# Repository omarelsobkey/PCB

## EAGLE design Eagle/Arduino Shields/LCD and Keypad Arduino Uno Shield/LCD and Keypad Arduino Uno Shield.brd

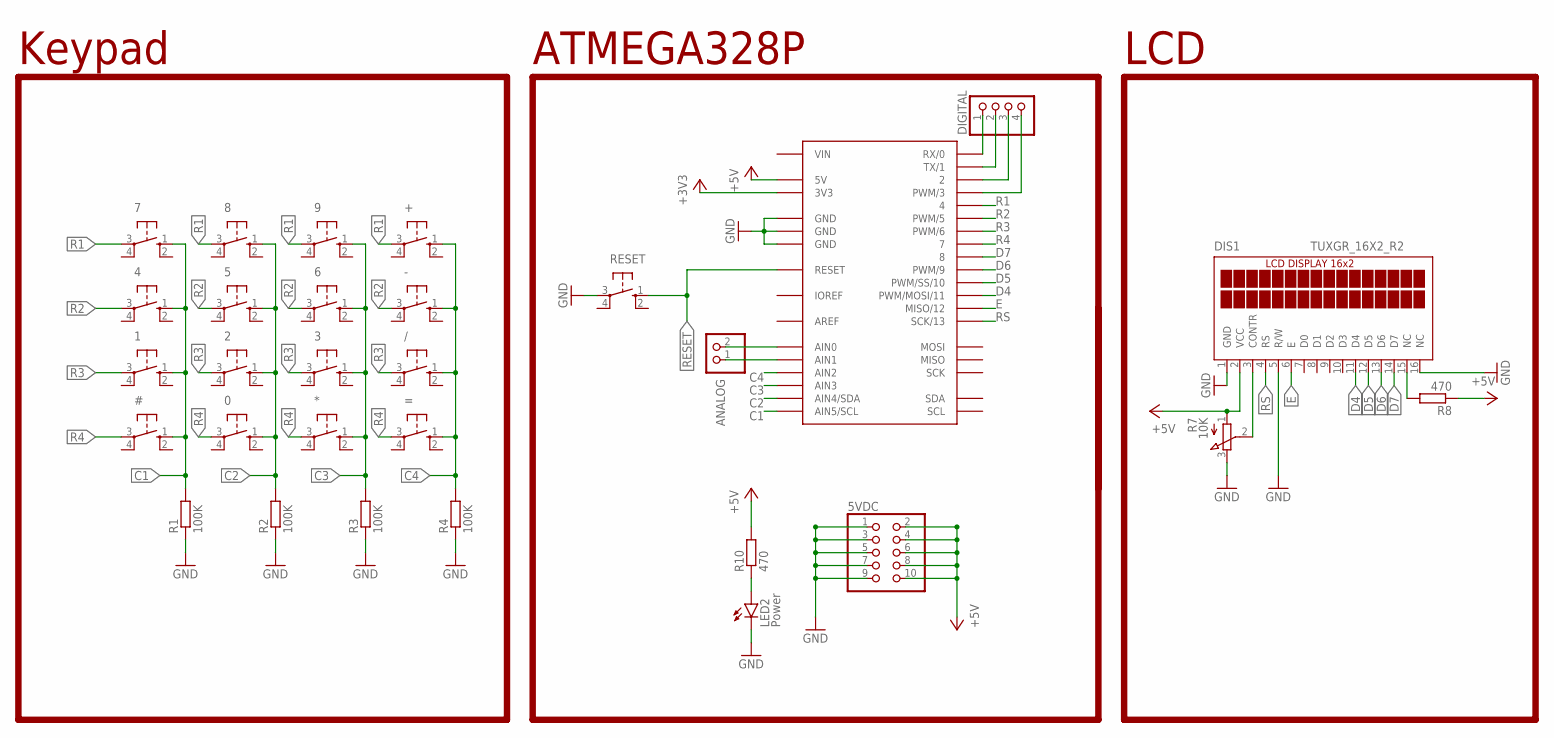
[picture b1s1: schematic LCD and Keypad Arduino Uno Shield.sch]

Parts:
0, 1, 2, 3, 4, 5, 6, 7, 8, 9: 10-XX; B3F-10XX
5VDC: PINHD-2X5; 2X05
#: 10-XX; B3F-10XX
*: 10-XX; B3F-10XX
+: 10-XX; B3F-10XX
-: 10-XX; B3F-10XX
/: 10-XX; B3F-10XX
=: 10-XX; B3F-10XX
ANALOG: PINHD-1X2; 1X02
ARD1: A-UNO_ISP-TP; A-UNO-ISP_TP
DIGITAL: PINHD-1X4; 1X04
DIS1: TUXGR_16X2_R2
LED2: Power; LED3MM
R1, R2, R3, R4: 100K; 0204/7
R7: 10K; 3RP/1610N
R8, R10: 470; 0204/7
RESET: 10-XX; B3F-10XX

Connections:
+3V3: ARD1.3V3
+5V: 5VDC.2, 5VDC.4, 5VDC.6, 5VDC.8, 5VDC.10, ARD1.5V, DIS1.2 (VCC), R7.1 (A), R8.1, R10.2
AREF: ARD1.AREF
C1: 1.1 (S), 4.1 (S), 7.1 (S), #.1 (S), ARD1.A5 (AIN5/SCL), R1.2
C2: 0.1 (S), 2.1 (S), 5.1 (S), 8.1 (S), ARD1.A4 (AIN4/SDA), R2.2
C3: 3.1 (S), 6.1 (S), 9.1 (S), *.1 (S), ARD1.A3 (AIN3), R3.2
C4: +.1 (S), -.1 (S), /.1 (S), =.1 (S), ARD1.A2 (AIN2), R4.2
D4: ARD1.11 (PWM/MOSI/11), DIS1.11 (D4)
D5: ARD1.10 (PWM/SS/10), DIS1.12 (D5)
D6: ARD1.9 (PWM/9), DIS1.13 (D6)
D7: ARD1.8, DIS1.14 (D7)
E: ARD1.12 (MISO/12), DIS1.6 (E)
GND: 5VDC.1, 5VDC.3, 5VDC.5, 5VDC.7, 5VDC.9, ARD1.GND@1 (GND), ARD1.GND@2 (GND), ARD1.GND@3 (GND), DIS1.1 (GND), DIS1.5 (R/W), DIS1.16 (NC), LED2.K (C), R1.1, R2.1, R3.1, R4.1, R7.3 (E), RESET.3
IOREF: ARD1.IOREF
unnamed: ANALOG.1, ARD1.A1 (AIN1)
unnamed: ANALOG.2, ARD1.A0 (AIN0)
unnamed: DIS1.3 (CONTR), R7.2 (S)
unnamed: DIS1.15 (NC), R8.2
unnamed: ARD1.3 (PWM/3), DIGITAL.4
unnamed: ARD1.2, DIGITAL.3
unnamed: ARD1.1 (TX/1), DIGITAL.2
unnamed: LED2.A, R10.1
unnamed: ARD1.0 (RX/0), DIGITAL.1
R1: 7.3, 8.3, 9.3, +.3, ARD1.4
R2: 4.3, 5.3, 6.3, -.3, ARD1.5 (PWM/5)
R3: 1.3, 2.3, 3.3, /.3, ARD1.6 (PWM/6)
R4: 0.3, #.3, *.3, =.3, ARD1.7
RESET: ARD1.RST (RESET), RESET.1 (S)
RS: ARD1.13 (SCK/13), DIS1.4 (RS)
VIN: ARD1.VIN

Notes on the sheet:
Keypad
LCD
ATMEGA328P

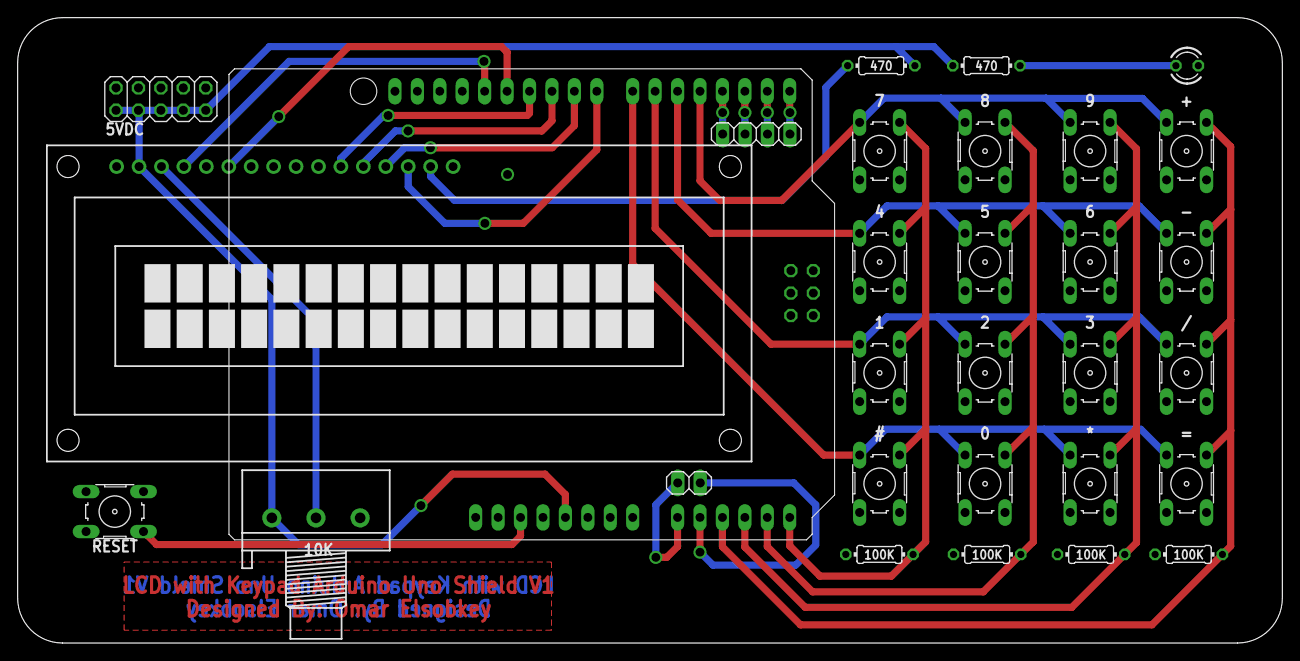
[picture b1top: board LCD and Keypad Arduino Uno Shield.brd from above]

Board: 2 copper layers, 143.2 x 70.8 mm, 30 parts (0 on the bottom side), 26 nets.

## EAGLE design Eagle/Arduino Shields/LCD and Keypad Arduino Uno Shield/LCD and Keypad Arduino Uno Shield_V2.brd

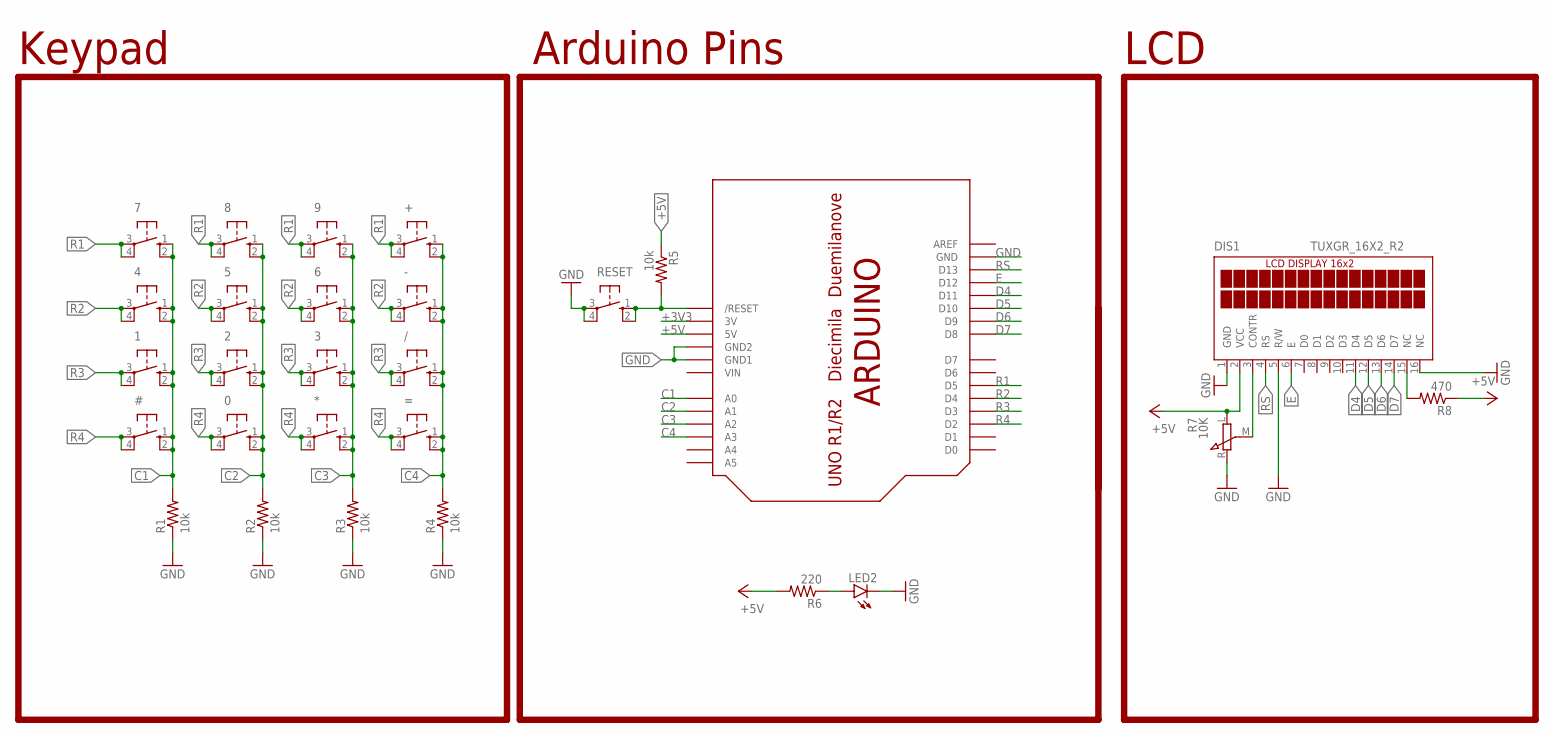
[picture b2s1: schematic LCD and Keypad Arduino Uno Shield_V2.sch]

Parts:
0, 1, 2, 3, 4, 5, 6, 7, 8, 9: 10-XX; B3F-10XX
#: 10-XX; B3F-10XX
*: 10-XX; B3F-10XX
+: 10-XX; B3F-10XX
-: 10-XX; B3F-10XX
/: 10-XX; B3F-10XX
=: 10-XX; B3F-10XX
DIS1: TUXGR_16X2_R2
LED2: LEDSML0805; SML0805
R1, R2, R3, R4, R5: 10k; 1206
R6: 220; 1206
R7: 10K; RM-065
R8: 470; 1206
RESET: 10-XX; B3F-10XX
U$1: ARDUINO-NODIM

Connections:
+3V3: U$1.3V
+5V: DIS1.2 (VCC), R5.1, R6.2, R7.L, R8.1, U$1.5V
C1: 1.1 (S), 1.2 (S1), 4.1 (S), 4.2 (S1), 7.1 (S), 7.2 (S1), #.1 (S), #.2 (S1), R1.2, U$1.A0
C2: 0.1 (S), 0.2 (S1), 2.1 (S), 2.2 (S1), 5.1 (S), 5.2 (S1), 8.1 (S), 8.2 (S1), R2.2, U$1.A1
C3: 3.1 (S), 3.2 (S1), 6.1 (S), 6.2 (S1), 9.1 (S), 9.2 (S1), *.1 (S), *.2 (S1), R3.2, U$1.A2
C4: +.1 (S), +.2 (S1), -.1 (S), -.2 (S1), /.1 (S), /.2 (S1), =.1 (S), =.2 (S1), R4.2, U$1.A3
D4: DIS1.11 (D4), U$1.D11
D5: DIS1.12 (D5), U$1.D10
D6: DIS1.13 (D6), U$1.D9
D7: DIS1.14 (D7), U$1.D8
E: DIS1.6 (E), U$1.D12
GND: DIS1.1 (GND), DIS1.5 (R/W), DIS1.16 (NC), LED2.C, R1.1, R2.1, R3.1, R4.1, R7.R, RESET.3, RESET.4 (P1), U$1.GND, U$1.GND1, U$1.GND2
unnamed: DIS1.3 (CONTR), R7.M
unnamed: DIS1.15 (NC), R8.2
unnamed: LED2.A, R6.1
R1: 7.3, 7.4 (P1), 8.3, 8.4 (P1), 9.3, 9.4 (P1), +.3, +.4 (P1), U$1.D5
R2: 4.3, 4.4 (P1), 5.3, 5.4 (P1), 6.3, 6.4 (P1), -.3, -.4 (P1), U$1.D4
R3: 1.3, 1.4 (P1), 2.3, 2.4 (P1), 3.3, 3.4 (P1), /.3, /.4 (P1), U$1.D3
R4: 0.3, 0.4 (P1), #.3, #.4 (P1), *.3, *.4 (P1), =.3, =.4 (P1), U$1.D2
RESET: R5.2, RESET.1 (S), RESET.2 (S1), U$1.RESET (/RESET)
RS: DIS1.4 (RS), U$1.D13
VIN: U$1.VIN

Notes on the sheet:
Keypad
LCD
Arduino Pins

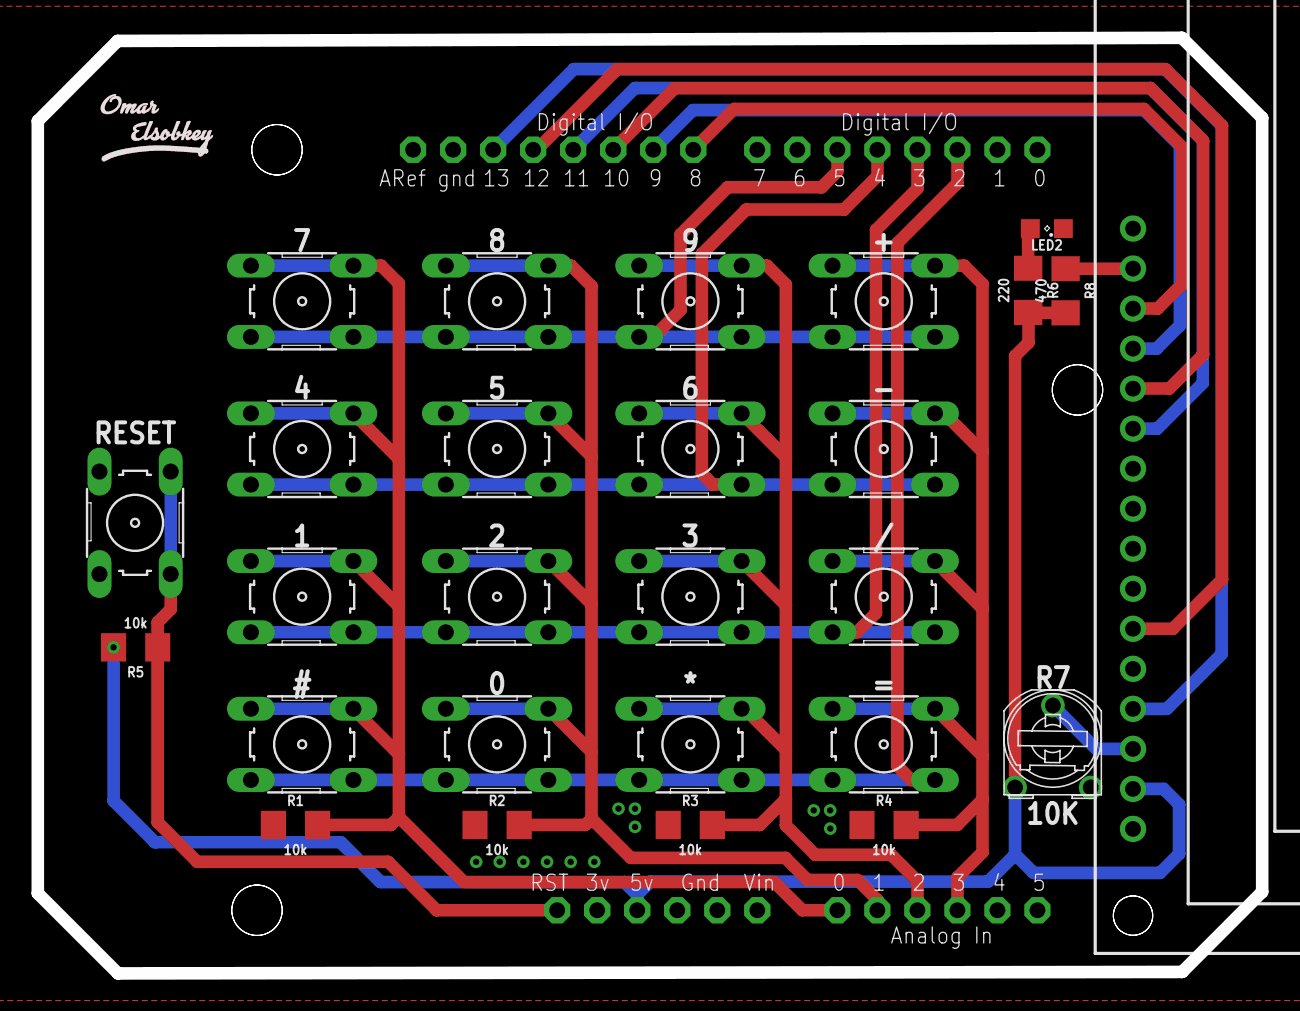
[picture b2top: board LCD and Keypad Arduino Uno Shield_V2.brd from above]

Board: 2 copper layers, 77.7 x 59.4 mm, 29 parts (0 on the bottom side), 20 nets.

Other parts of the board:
U$2: OMAR_ELSOBKEY_X0.5

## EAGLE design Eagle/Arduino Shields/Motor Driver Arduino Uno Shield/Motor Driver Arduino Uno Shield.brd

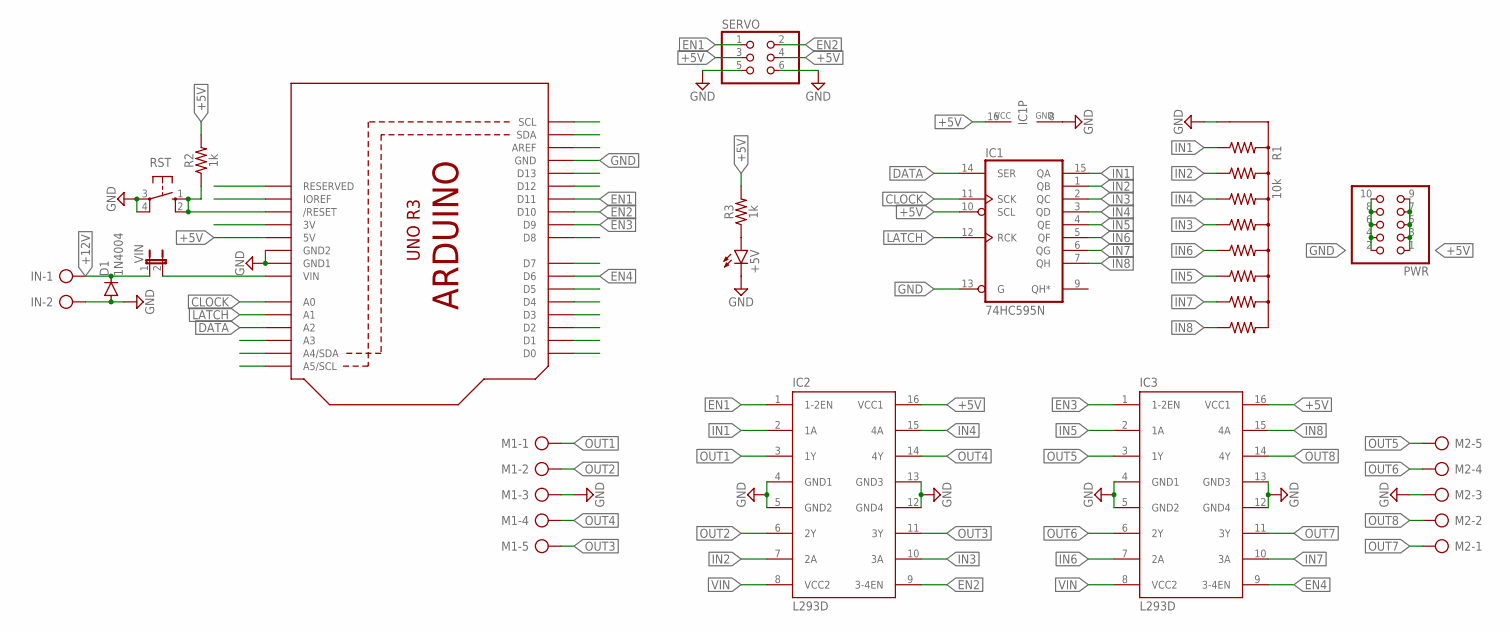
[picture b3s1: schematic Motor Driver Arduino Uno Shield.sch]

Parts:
+5V: LEDCHIP-LED0805; CHIP-LED0805
D1: 1N4004; DO41-10
IC1: 74HC595N; DIL16
IC2, IC3: L293D; DIL16
IN: AK500/2-H
M1, M2: AK500/5-H
PWR: PINHD-2X5; 2X05
R1: 10k; 4609X-101-103LF
R2, R3: 1k; 1206
RST: 10-XX; B3F-10XX
SERVO: PINHD-2X3; 2X03
U1: ARDUINOR3-BPLACE
VIN: JP1E; JP1

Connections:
+5V: IC1.10 (SCL), IC1.16 (VCC), IC2.16 (VCC1), IC3.16 (VCC1), PWR.1, PWR.3, PWR.5, PWR.7, PWR.9, R2.2, R3.2, SERVO.3, SERVO.4, U1.5V
+12V: D1.C, IN.1, VIN.1
AREF: U1.AREF
CLOCK: IC1.11 (SCK), U1.A0
D2: U1.D2
D3: U1.D3
D4: U1.D4
D5: U1.D5
D7: U1.D7
D8: U1.D8
D12: U1.D12
D13: U1.D13
DATA: IC1.14 (SER), U1.A2
EN1: IC2.1 (1-2EN), SERVO.1, U1.D11
EN2: IC2.9 (3-4EN), SERVO.2, U1.D10
EN3: IC3.1 (1-2EN), U1.D9
EN4: IC3.9 (3-4EN), U1.D6
GND: +5V.C, D1.A, IC1.8 (GND), IC1.13 (G), IC2.4 (GND1), IC2.5 (GND2), IC2.12 (GND4), IC2.13 (GND3), IC3.4 (GND1), IC3.5 (GND2), IC3.12 (GND4), IC3.13 (GND3), IN.2, M1.3, M2.3, PWR.2, PWR.4, PWR.6, PWR.8, PWR.10, R1.1, RST.3, RST.4 (P1), SERVO.5, SERVO.6, U1.GND, U1.GND1, U1.GND2
IN1: IC1.15 (QA), IC2.2 (1A), R1.2
IN2: IC1.1 (QB), IC2.7 (2A), R1.3
IN3: IC1.2 (QC), IC2.10 (3A), R1.5
IN4: IC1.3 (QD), IC2.15 (4A), R1.4
IN5: IC1.4 (QE), IC3.2 (1A), R1.7
IN6: IC1.5 (QF), IC3.7 (2A), R1.6
IN7: IC1.6 (QG), IC3.10 (3A), R1.8
IN8: IC1.7 (QH), IC3.15 (4A), R1.9
LATCH: IC1.12 (RCK), U1.A1
unnamed: +5V.A, R3.1
OUT1: IC2.3 (1Y), M1.1
OUT2: IC2.6 (2Y), M1.2
OUT3: IC2.11 (3Y), M1.5
OUT4: IC2.14 (4Y), M1.4
OUT5: IC3.3 (1Y), M2.5
OUT6: IC3.6 (2Y), M2.4
OUT7: IC3.11 (3Y), M2.1
OUT8: IC3.14 (4Y), M2.2
RST: R2.1, RST.1 (S), RST.2 (S1), U1.RESET (/RESET)
SCL: U1.SCL
SDA: U1.SDA
VIN: IC2.8 (VCC2), IC3.8 (VCC2), U1.VIN, VIN.2

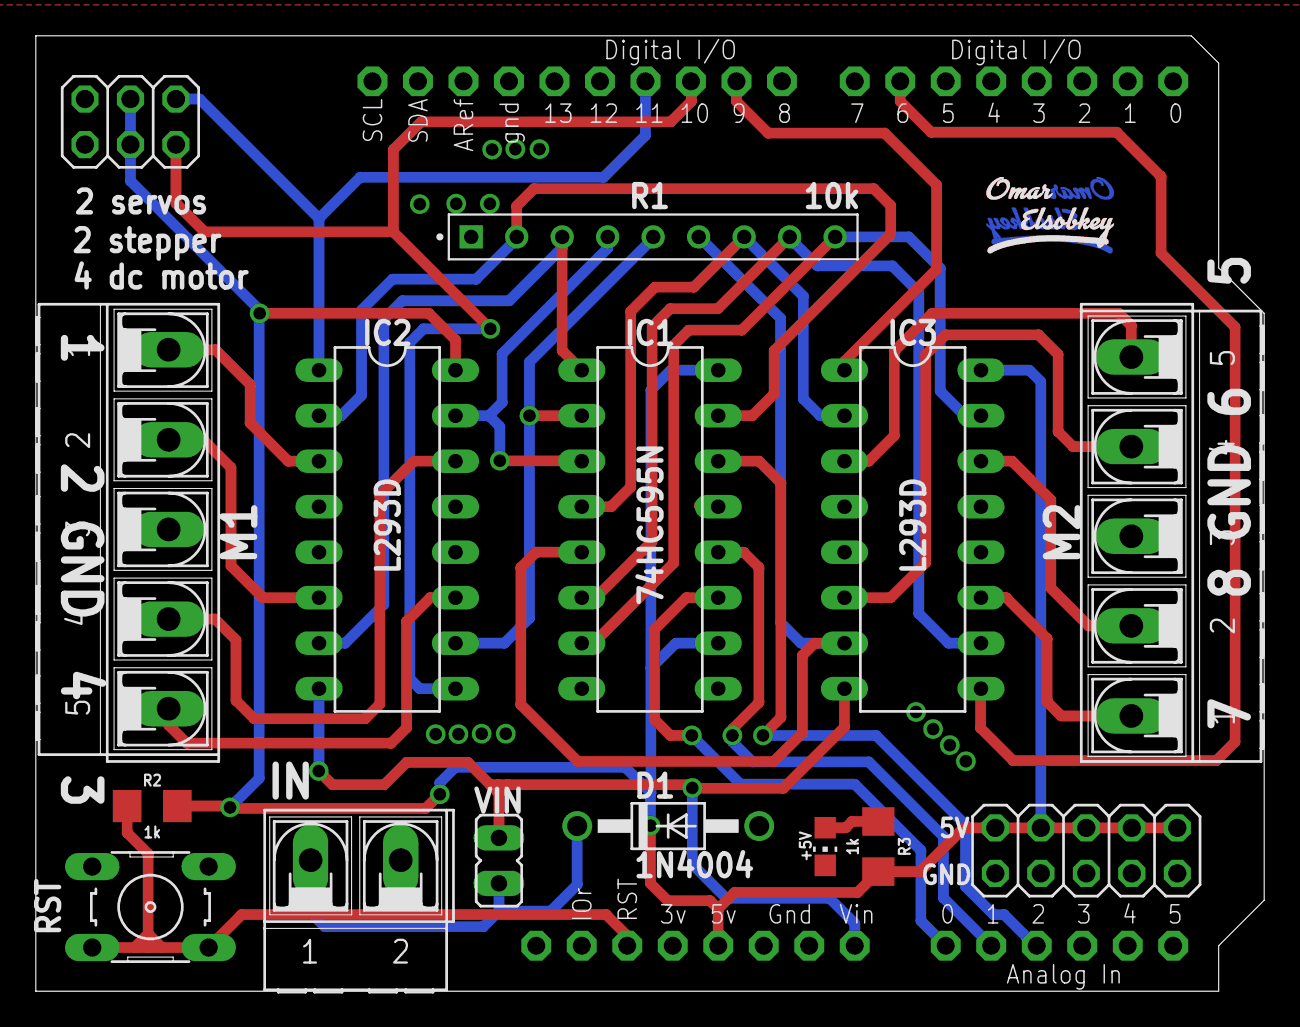
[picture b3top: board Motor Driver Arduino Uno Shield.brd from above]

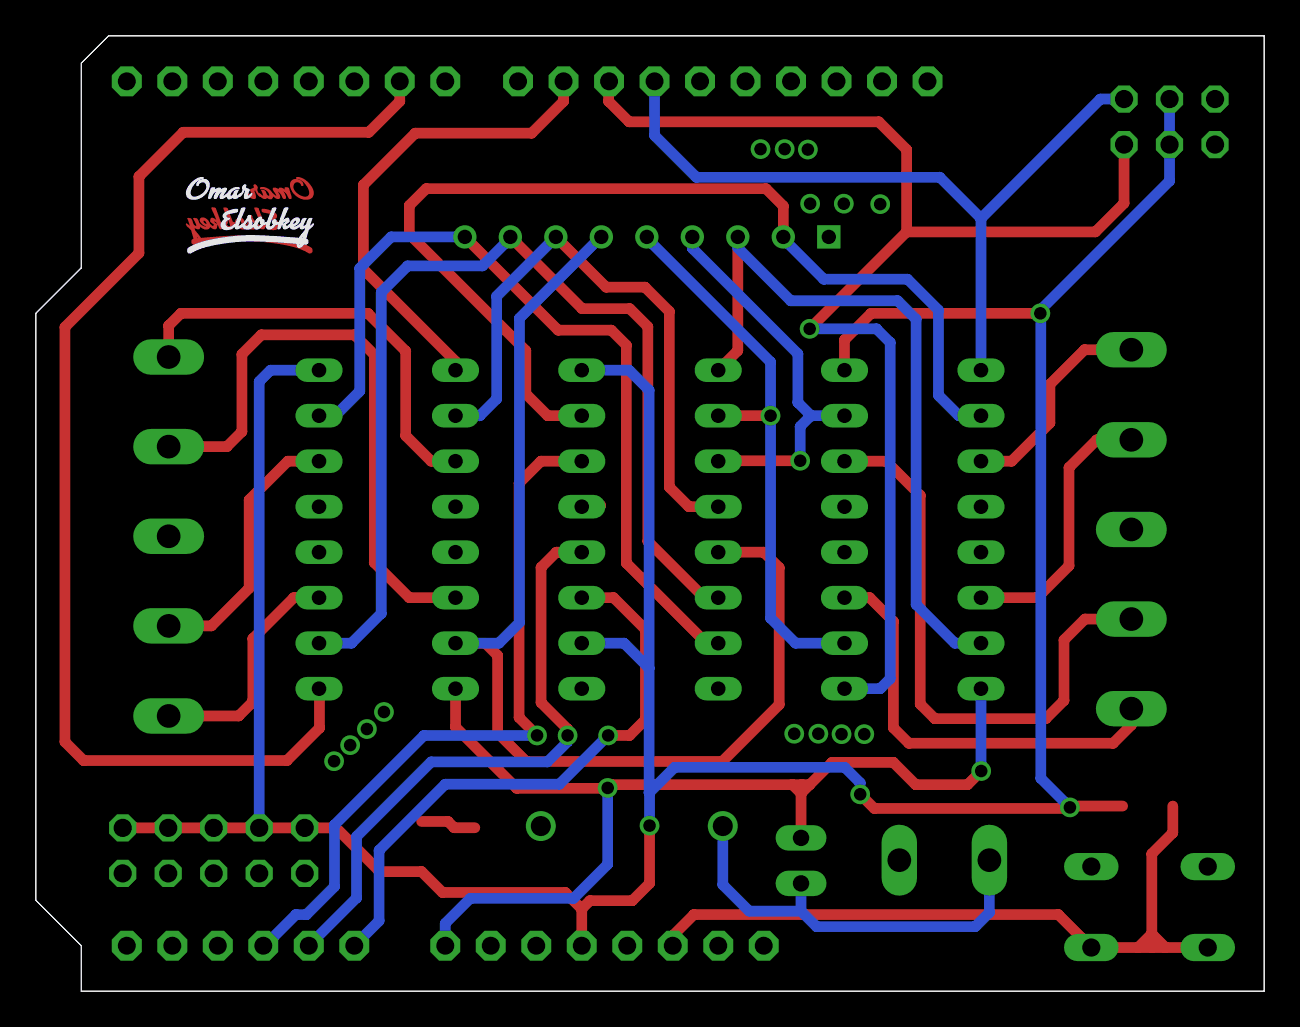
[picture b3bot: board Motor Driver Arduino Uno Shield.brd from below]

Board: 2 copper layers, 68.6 x 53.3 mm, 20 parts (2 on the bottom side), 29 nets.

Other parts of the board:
U$1, U$3: OMAR_ELSOBKEY_X0.5_TN
U$2, U$4: OMAR_ELSOBKEY_X0.5_T

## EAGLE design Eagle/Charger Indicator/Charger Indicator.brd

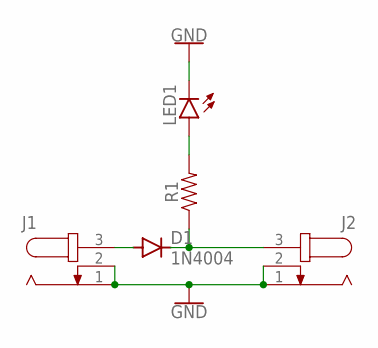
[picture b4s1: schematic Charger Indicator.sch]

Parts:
D1: 1N4004; DO41-10
J1, J2: JACK-PLUG0; SPC4077
LED1: LED3MM
R1: 1206

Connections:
GND: J1.1, J1.2, J2.1, J2.2, LED1.K (C)
unnamed: D1.A, J1.3
unnamed: D1.C, J2.3, R1.1
unnamed: LED1.A, R1.2

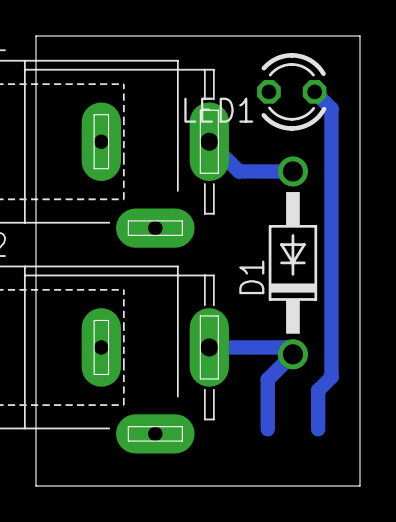
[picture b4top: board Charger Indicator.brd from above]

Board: 2 copper layers, 18.0 x 25.0 mm, 5 parts (1 on the bottom side), 4 nets.

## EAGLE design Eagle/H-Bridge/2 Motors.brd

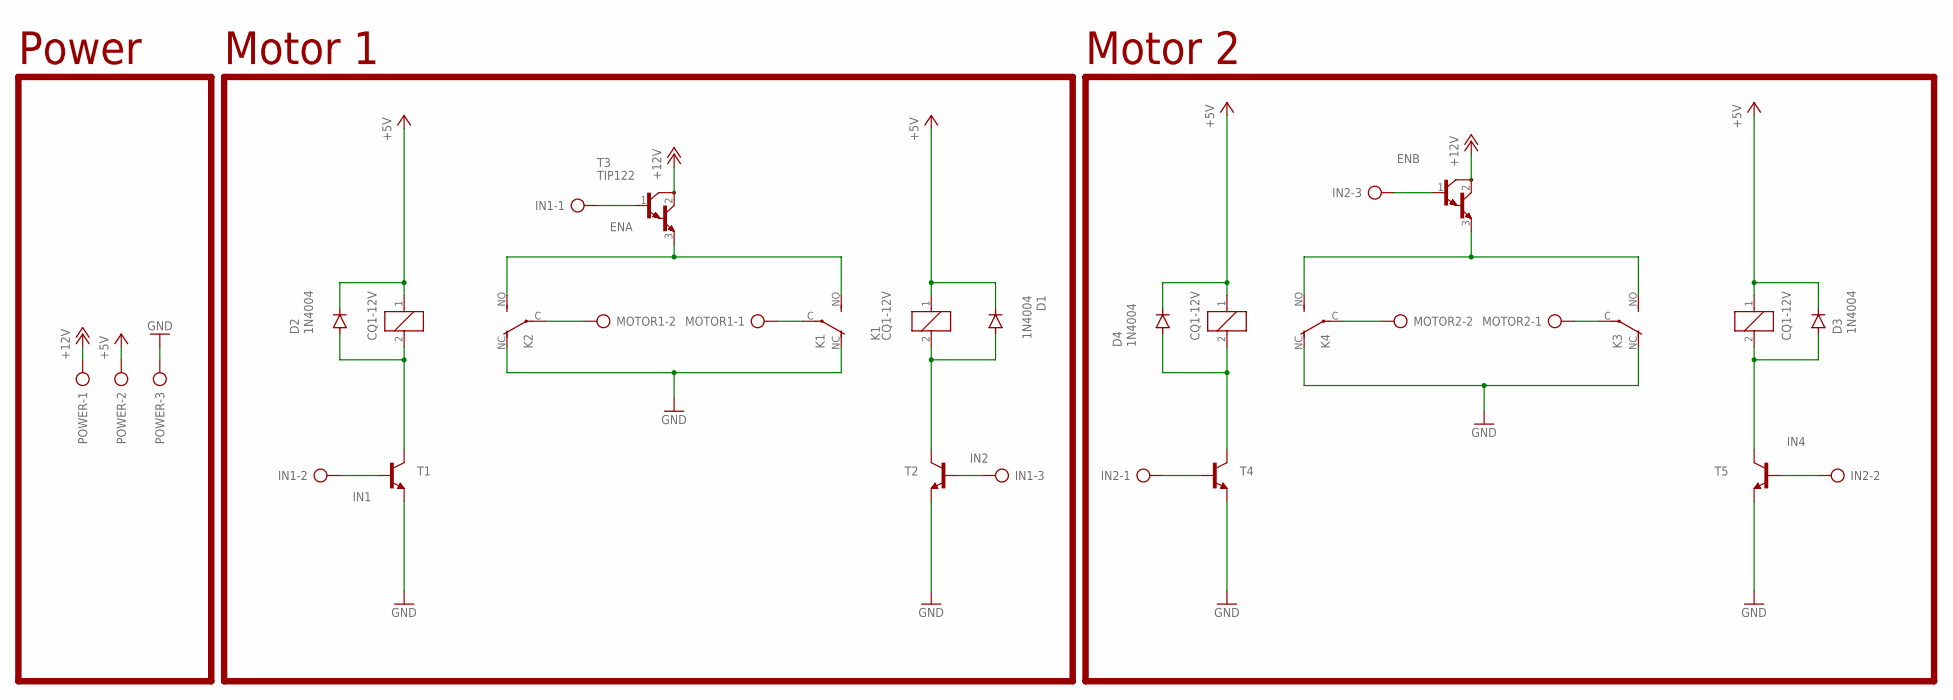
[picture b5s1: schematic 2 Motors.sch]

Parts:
D1, D2, D3, D4: 1N4004; DO41-10
IN1, IN2: AK300/3
K1, K2, K3, K4: CQ1-12V; CQ1
MOTOR1, MOTOR2: AK300/2
POWER: AK300/3
T1, T2, T4, T5: 2N2222-NPN-TO92-EBC; TO92-EBC
T3, T6: TIP122; TO220

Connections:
+5V: D1.C, D2.C, D3.C, D4.C, K1.1, K2.1, K3.1, K4.1, POWER.2
+12V: POWER.1, T3.2 (C), T6.2 (C)
ENA: IN1.1, T3.1 (B)
ENB: IN2.3, T6.1 (B)
GND: K1.NC (O), K2.NC (O), K3.NC (O), K4.NC (O), POWER.3, T1.E, T2.E, T4.E, T5.E
IN1: IN1.2, T1.B
IN2: IN1.3, T2.B
IN3: IN2.1, T4.B
IN4: IN2.2, T5.B
unnamed: K2.C, MOTOR1.2
unnamed: K1.NO (S), K2.NO (S), T3.3 (E)
unnamed: D2.A, K2.2, T1.C
unnamed: K1.C, MOTOR1.1
unnamed: D1.A, K1.2, T2.C
unnamed: D3.A, K3.2, T5.C
unnamed: K3.NO (S), K4.NO (S), T6.3 (E)
unnamed: D4.A, K4.2, T4.C
unnamed: K3.C, MOTOR2.1
unnamed: K4.C, MOTOR2.2

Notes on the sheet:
Power
Motor 1
Motor 2

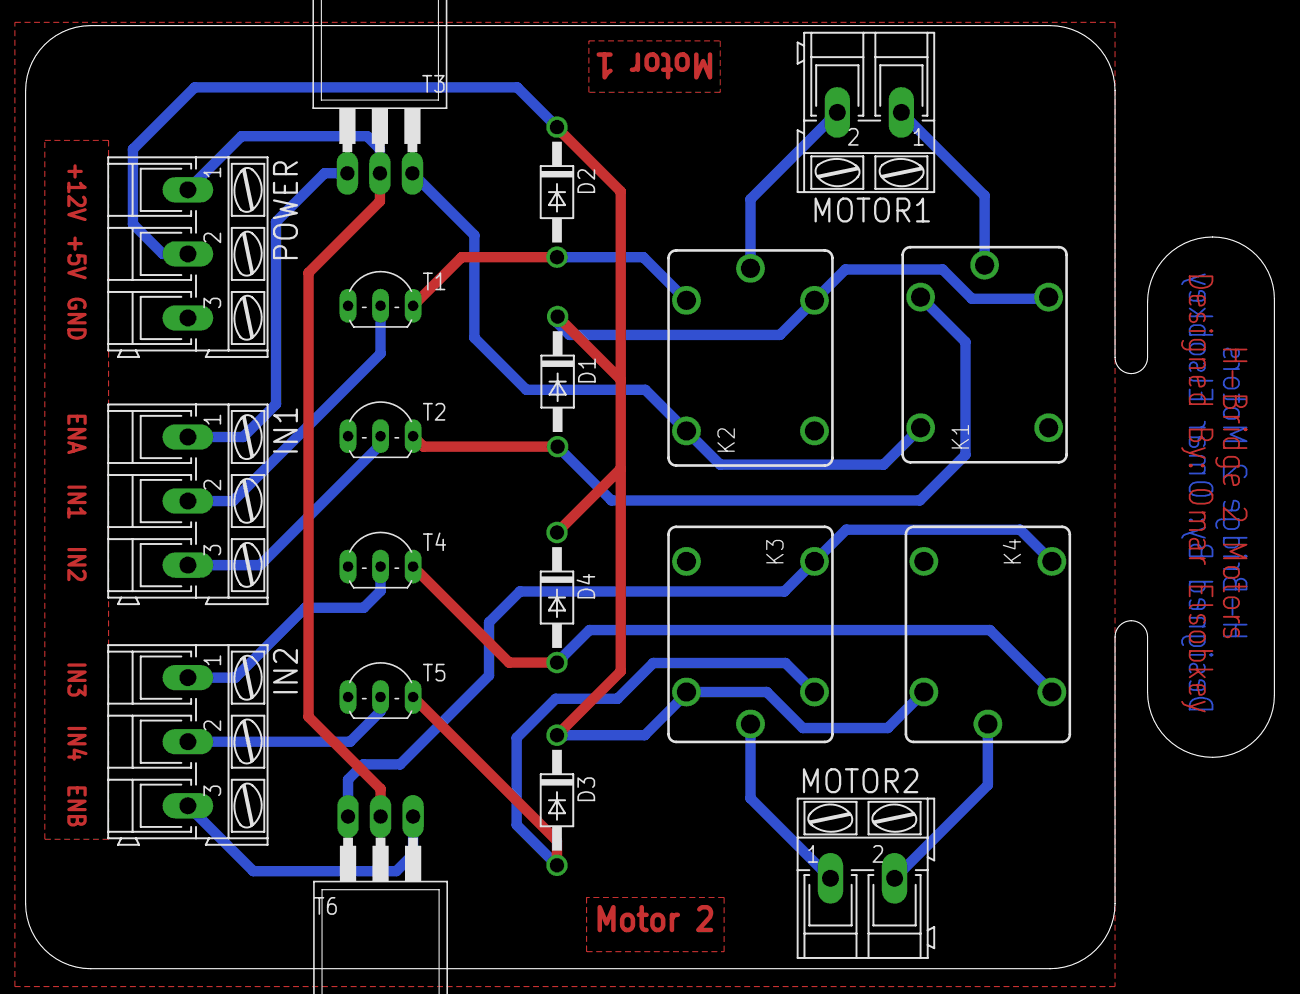
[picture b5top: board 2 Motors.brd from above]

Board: 2 copper layers, 97.5 x 73.7 mm, 19 parts (0 on the bottom side), 19 nets.

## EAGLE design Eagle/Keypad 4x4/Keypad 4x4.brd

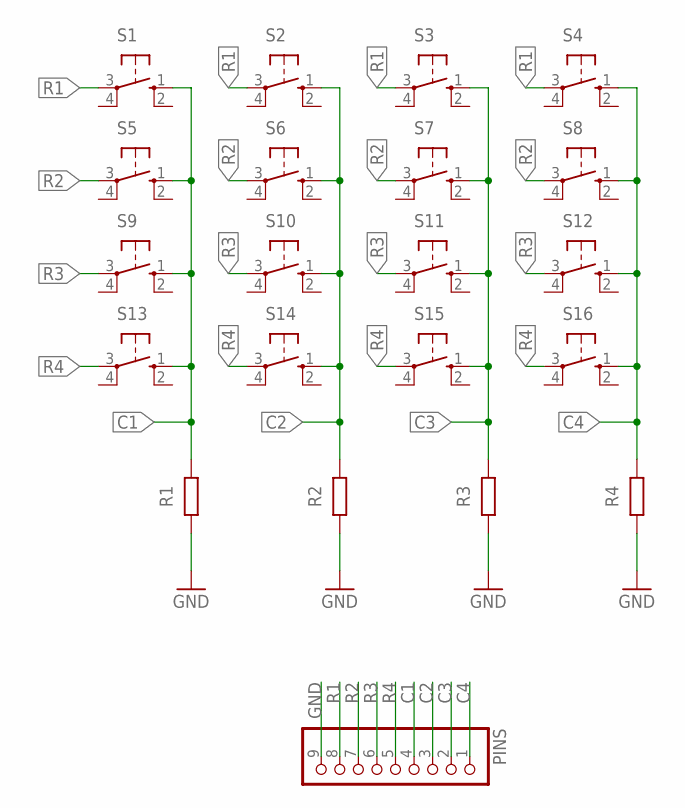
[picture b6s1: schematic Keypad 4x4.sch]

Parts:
PINS: PINHD-1X9/90; 1X09/90
R1, R2, R3, R4: 100k; 0204/7
S1, S2, S3, S4, S5, S6, S7, S8, S9, S10, S11, S12, S13, S14, S15, S16: 10-XX; B3F-10XX

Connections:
C1: PINS.4, R1.2, S1.1 (S), S5.1 (S), S9.1 (S), S13.1 (S)
C2: PINS.3, R2.2, S2.1 (S), S6.1 (S), S10.1 (S), S14.1 (S)
C3: PINS.2, R3.2, S3.1 (S), S7.1 (S), S11.1 (S), S15.1 (S)
C4: PINS.1, R4.2, S4.1 (S), S8.1 (S), S12.1 (S), S16.1 (S)
GND: PINS.9, R1.1, R2.1, R3.1, R4.1
R1: PINS.8, S1.3, S2.3, S3.3, S4.3
R2: PINS.7, S5.3, S6.3, S7.3, S8.3
R3: PINS.6, S9.3, S10.3, S11.3, S12.3
R4: PINS.5, S13.3, S14.3, S15.3, S16.3

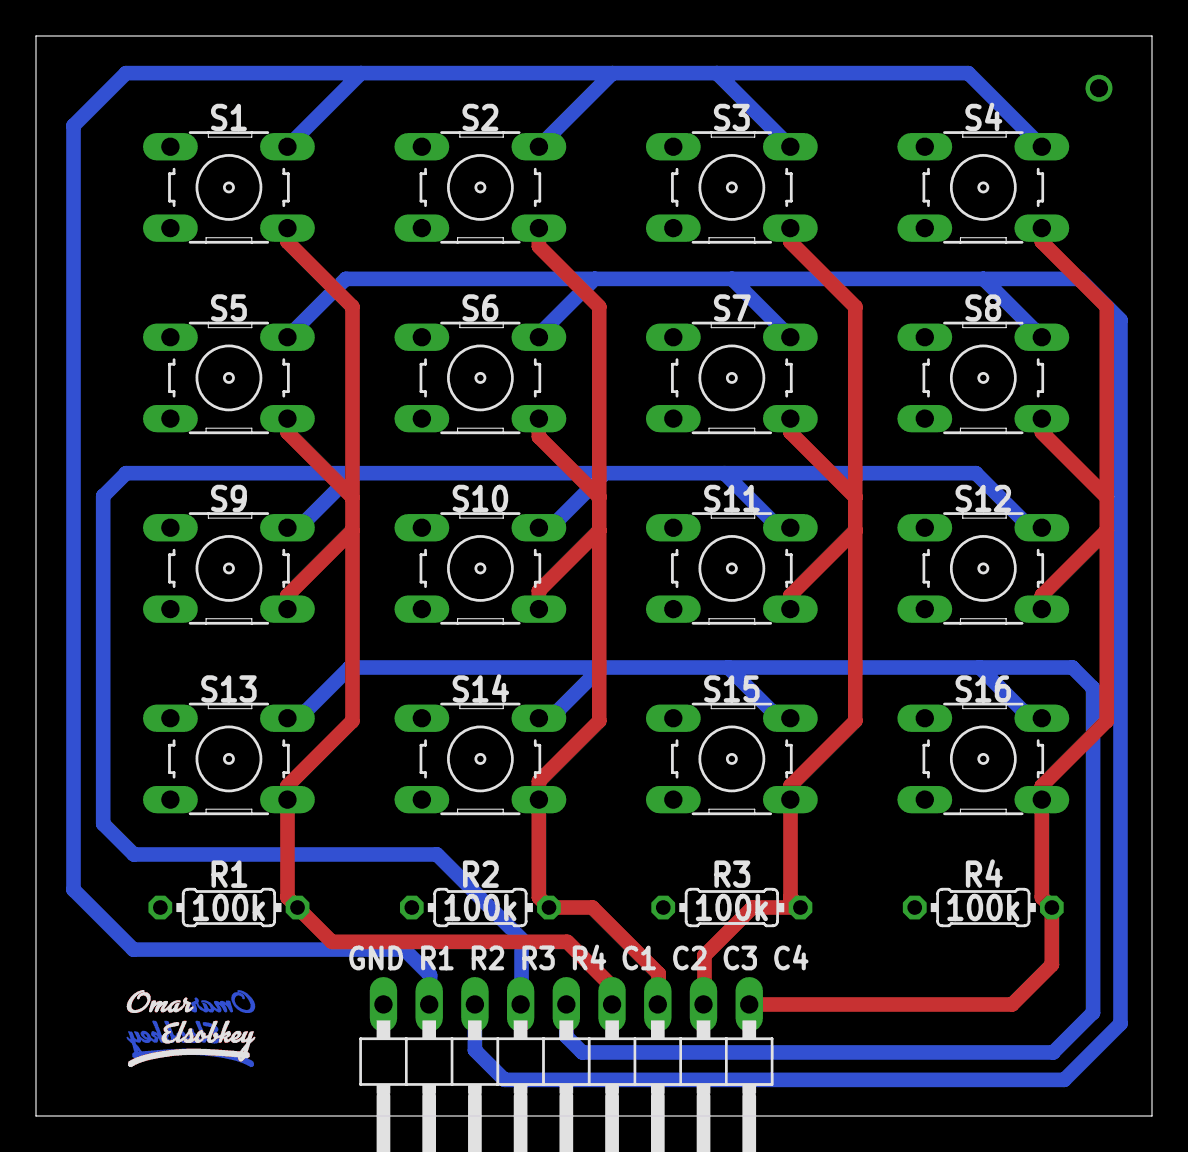
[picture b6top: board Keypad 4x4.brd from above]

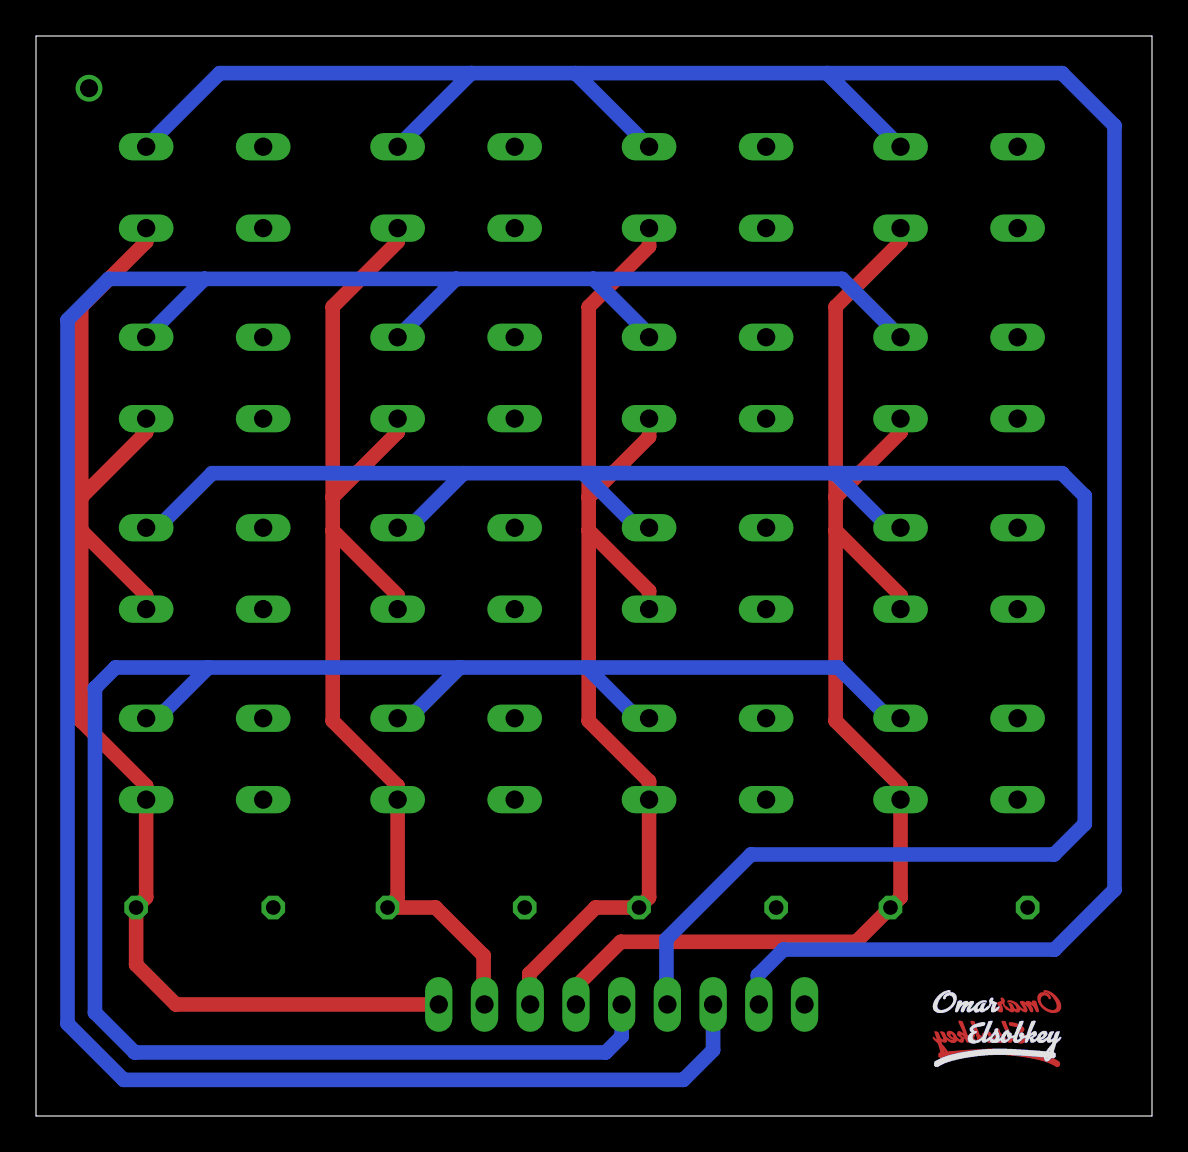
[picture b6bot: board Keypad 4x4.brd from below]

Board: 2 copper layers, 62.0 x 60.0 mm, 25 parts (2 on the bottom side), 9 nets.

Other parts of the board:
U$1, U$2: OMAR_ELSOBKEY_X0.5_T
U$3, U$4: OMAR_ELSOBKEY_X0.5_TN

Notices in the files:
parts and their libraries:
SparkFun-Resistors: Licensing: Creative Commons ShareAlike 4.0 International - https://creativecommons.org/licenses/by-sa/4.0
